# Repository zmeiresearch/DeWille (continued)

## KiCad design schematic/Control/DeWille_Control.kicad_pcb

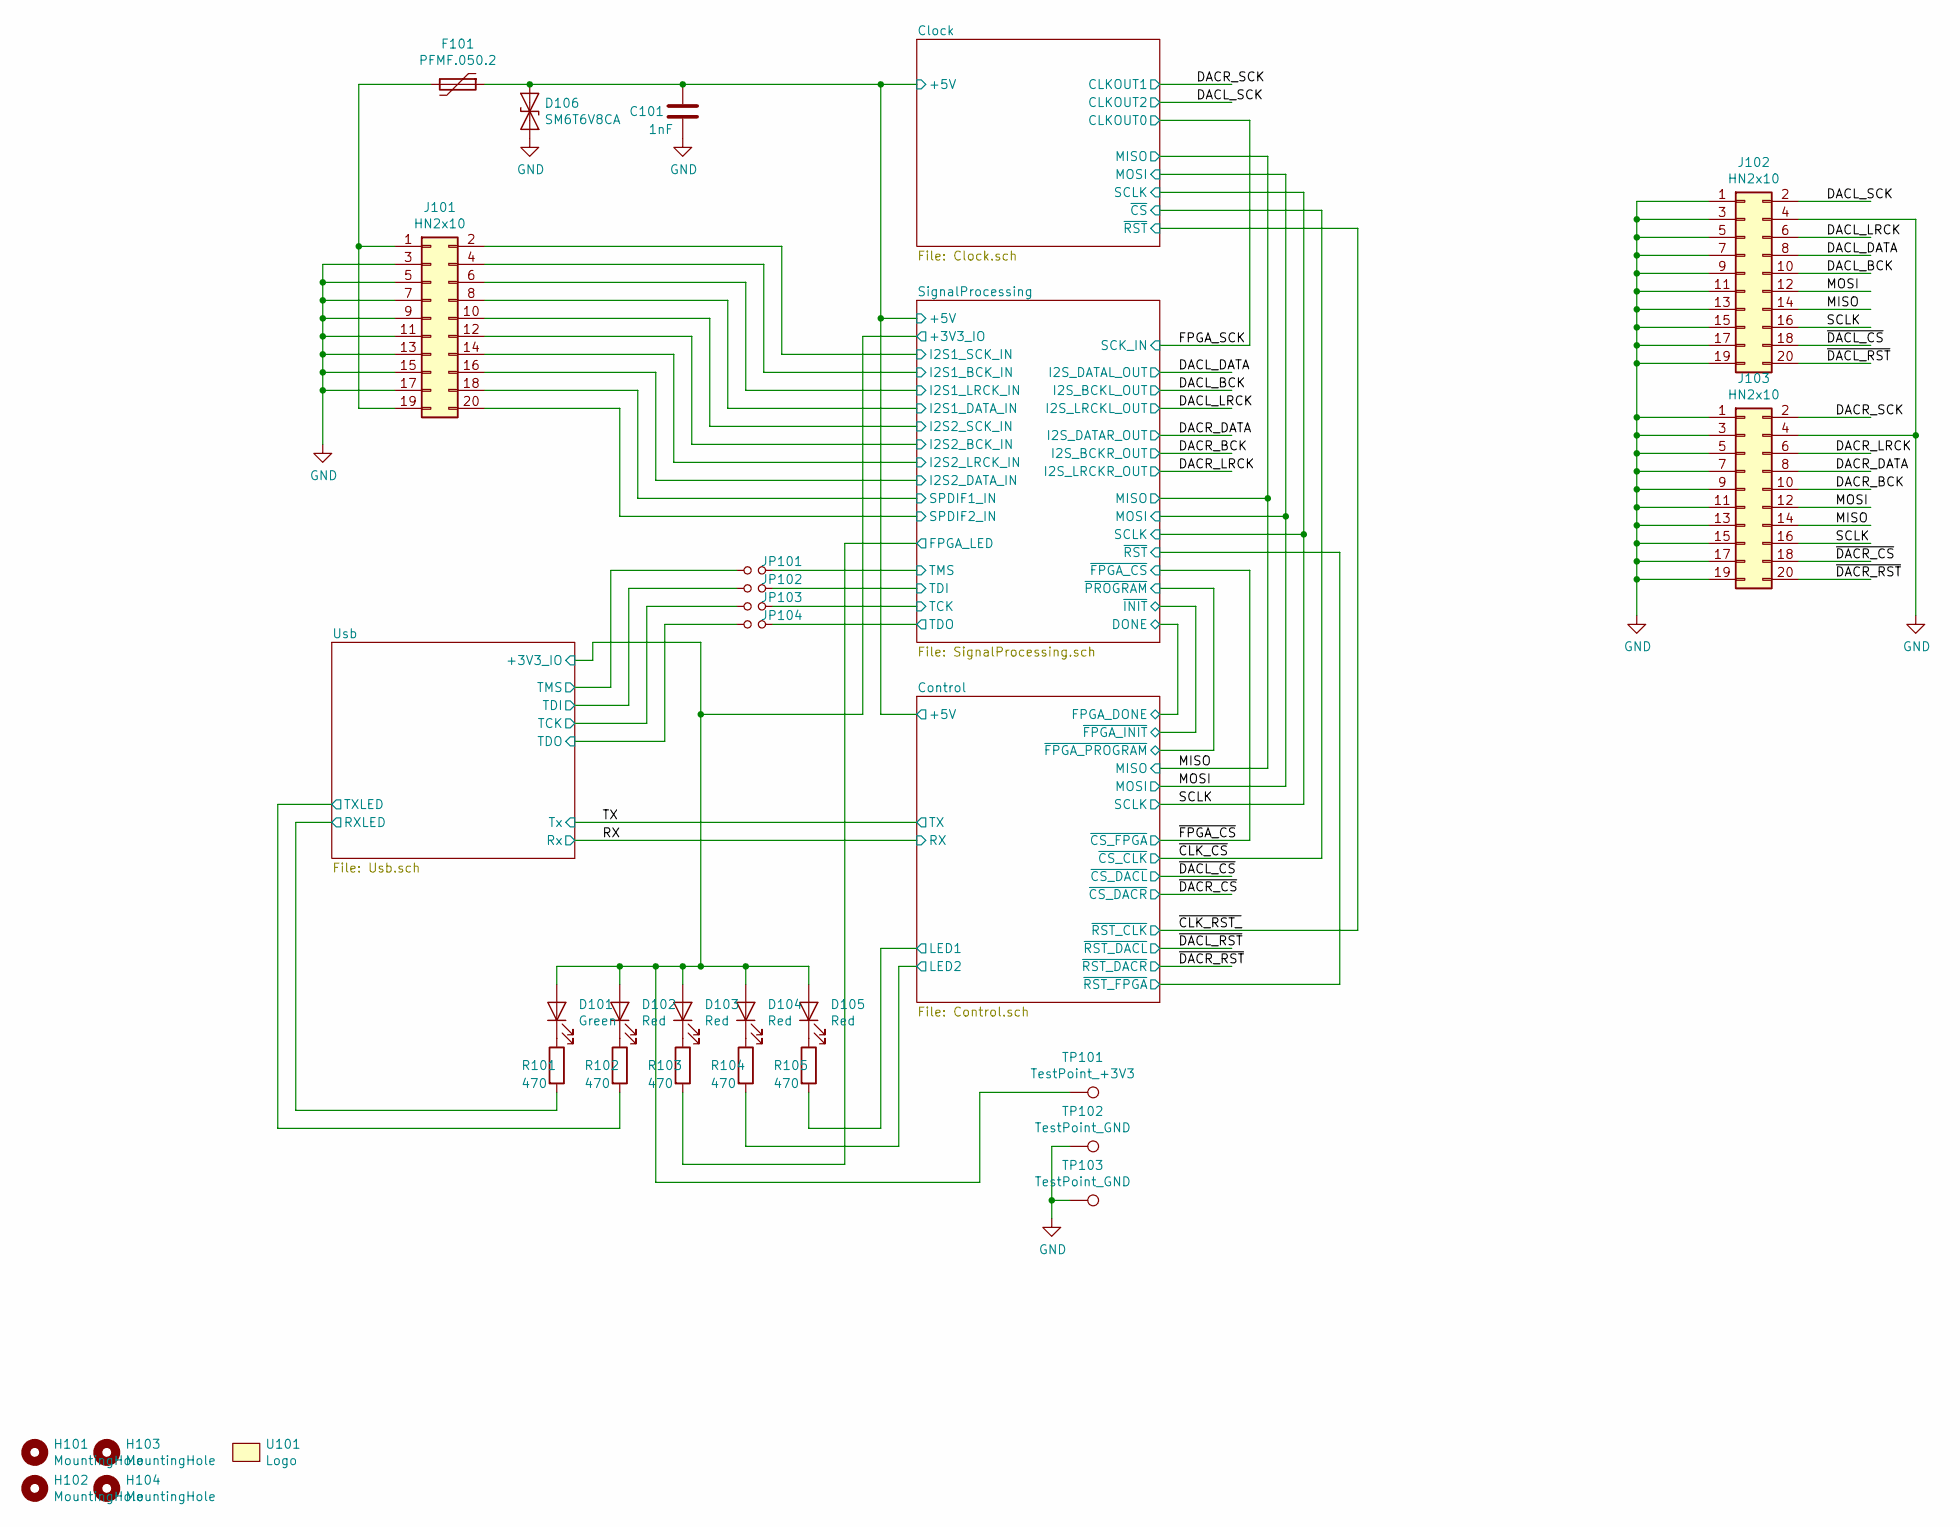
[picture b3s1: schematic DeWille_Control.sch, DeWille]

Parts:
C101: 1nF; C_0603_1608Metric
D101: Green; LED_0805_2012Metric
D102, D103, D104, D105: Red; LED_0805_2012Metric
D106: SM6T6V8CA; D_SMB
F101: PFMF.050.2; Fuse_1812_4532Metric
H101, H102, H103, H104: MountingHole; MountingHole_3.2mm_M3_Pad
J101, J102, J103: HN2x10; PinHeader_2x10_P2.54mm_Vertical
JP101, JP102, JP103, JP104: SolderJumper-2_P1.3mm_Bridged_RoundedPad1.0x1.5mm
R101, R102, R103, R104, R105: 470; R_0603_1608Metric
TP101: TestPoint_+3V3; TestPoint_THTPad_D2.0mm_Drill1.0mm
TP102, TP103: TestPoint_GND; TestPoint_THTPad_D2.0mm_Drill1.0mm
U101: Logo; Zmei-logo-small-inverted_nosilk

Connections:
/Clock/+5V: C101.2, D106.1 (A1), F101.1; also elsewhere on the board
/Control/LED1: R105.2; also elsewhere on the board
/Control/LED2: R104.2; also elsewhere on the board
/DACL_BCK: J102.10; also elsewhere on the board
/DACL_DATA: J102.8; also elsewhere on the board
/DACL_LRCK: J102.6; also elsewhere on the board
/DACL_SCK: J102.2; also elsewhere on the board
/DACR_BCK: J103.10; also elsewhere on the board
/DACR_DATA: J103.8; also elsewhere on the board
/DACR_LRCK: J103.6; also elsewhere on the board
/DACR_SCK: J103.2; also elsewhere on the board
/MISO: J102.14, J103.14; also elsewhere on the board
/MOSI: J102.12, J103.12; also elsewhere on the board
/SCLK: J102.16, J103.16; also elsewhere on the board
/SignalProcessing/+3V3_IO: D101.2 (A), D102.2 (A), D103.2 (A), D104.2 (A), D105.2 (A), TP101.1; also elsewhere on the board
/SignalProcessing/FPGA_LED: R103.2; also elsewhere on the board
/SignalProcessing/I2S1_BCK_IN: J101.4; also elsewhere on the board
/SignalProcessing/I2S1_DATA_IN: J101.8; also elsewhere on the board
/SignalProcessing/I2S1_LRCK_IN: J101.6; also elsewhere on the board
/SignalProcessing/I2S1_SCK_IN: J101.2; also elsewhere on the board
/SignalProcessing/I2S2_BCK_IN: J101.12; also elsewhere on the board
/SignalProcessing/I2S2_DATA_IN: J101.16; also elsewhere on the board
/SignalProcessing/I2S2_LRCK_IN: J101.14; also elsewhere on the board
/SignalProcessing/I2S2_SCK_IN: J101.10; also elsewhere on the board
/SignalProcessing/SPDIF1_IN: J101.18; also elsewhere on the board
/SignalProcessing/SPDIF2_IN: J101.20; also elsewhere on the board
/SignalProcessing/TCK: JP103.2; also elsewhere on the board
/SignalProcessing/TDI: JP102.2; also elsewhere on the board
/SignalProcessing/TDO: JP104.2; also elsewhere on the board
/SignalProcessing/TMS: JP101.2; also elsewhere on the board
/Usb/RXLED: R101.2; also elsewhere on the board
/Usb/TCK: JP103.1; also elsewhere on the board
/Usb/TDI: JP102.1; also elsewhere on the board
/Usb/TDO: JP104.1; also elsewhere on the board
/Usb/TMS: JP101.1; also elsewhere on the board
/Usb/TXLED: R102.2; also elsewhere on the board
/~DACL_CS~: J102.18; also elsewhere on the board
/~DACL_RST~: J102.20; also elsewhere on the board
/~DACR_CS~: J103.18; also elsewhere on the board
/~DACR_RST~: J103.20; also elsewhere on the board
GND: C101.1, D106.2 (A2), J101.3, J101.5, J101.7, J101.9, J101.11, J101.13, J101.15, J101.17, J102.1, J102.3, J102.4, J102.5, J102.7, J102.9, J102.11, J102.13, J102.15, J102.17, J102.19, J103.1, J103.3, J103.4, J103.5, J103.7, J103.9, J103.11, J103.13, J103.15, J103.17, J103.19, TP102.1, TP103.1; also elsewhere on the board
unnamed: D101.1 (K), R101.1
unnamed: D102.1 (K), R102.1
unnamed: D103.1 (K), R103.1
unnamed: D104.1 (K), R104.1
unnamed: D105.1 (K), R105.1
unnamed: F101.2, J101.1, J101.19

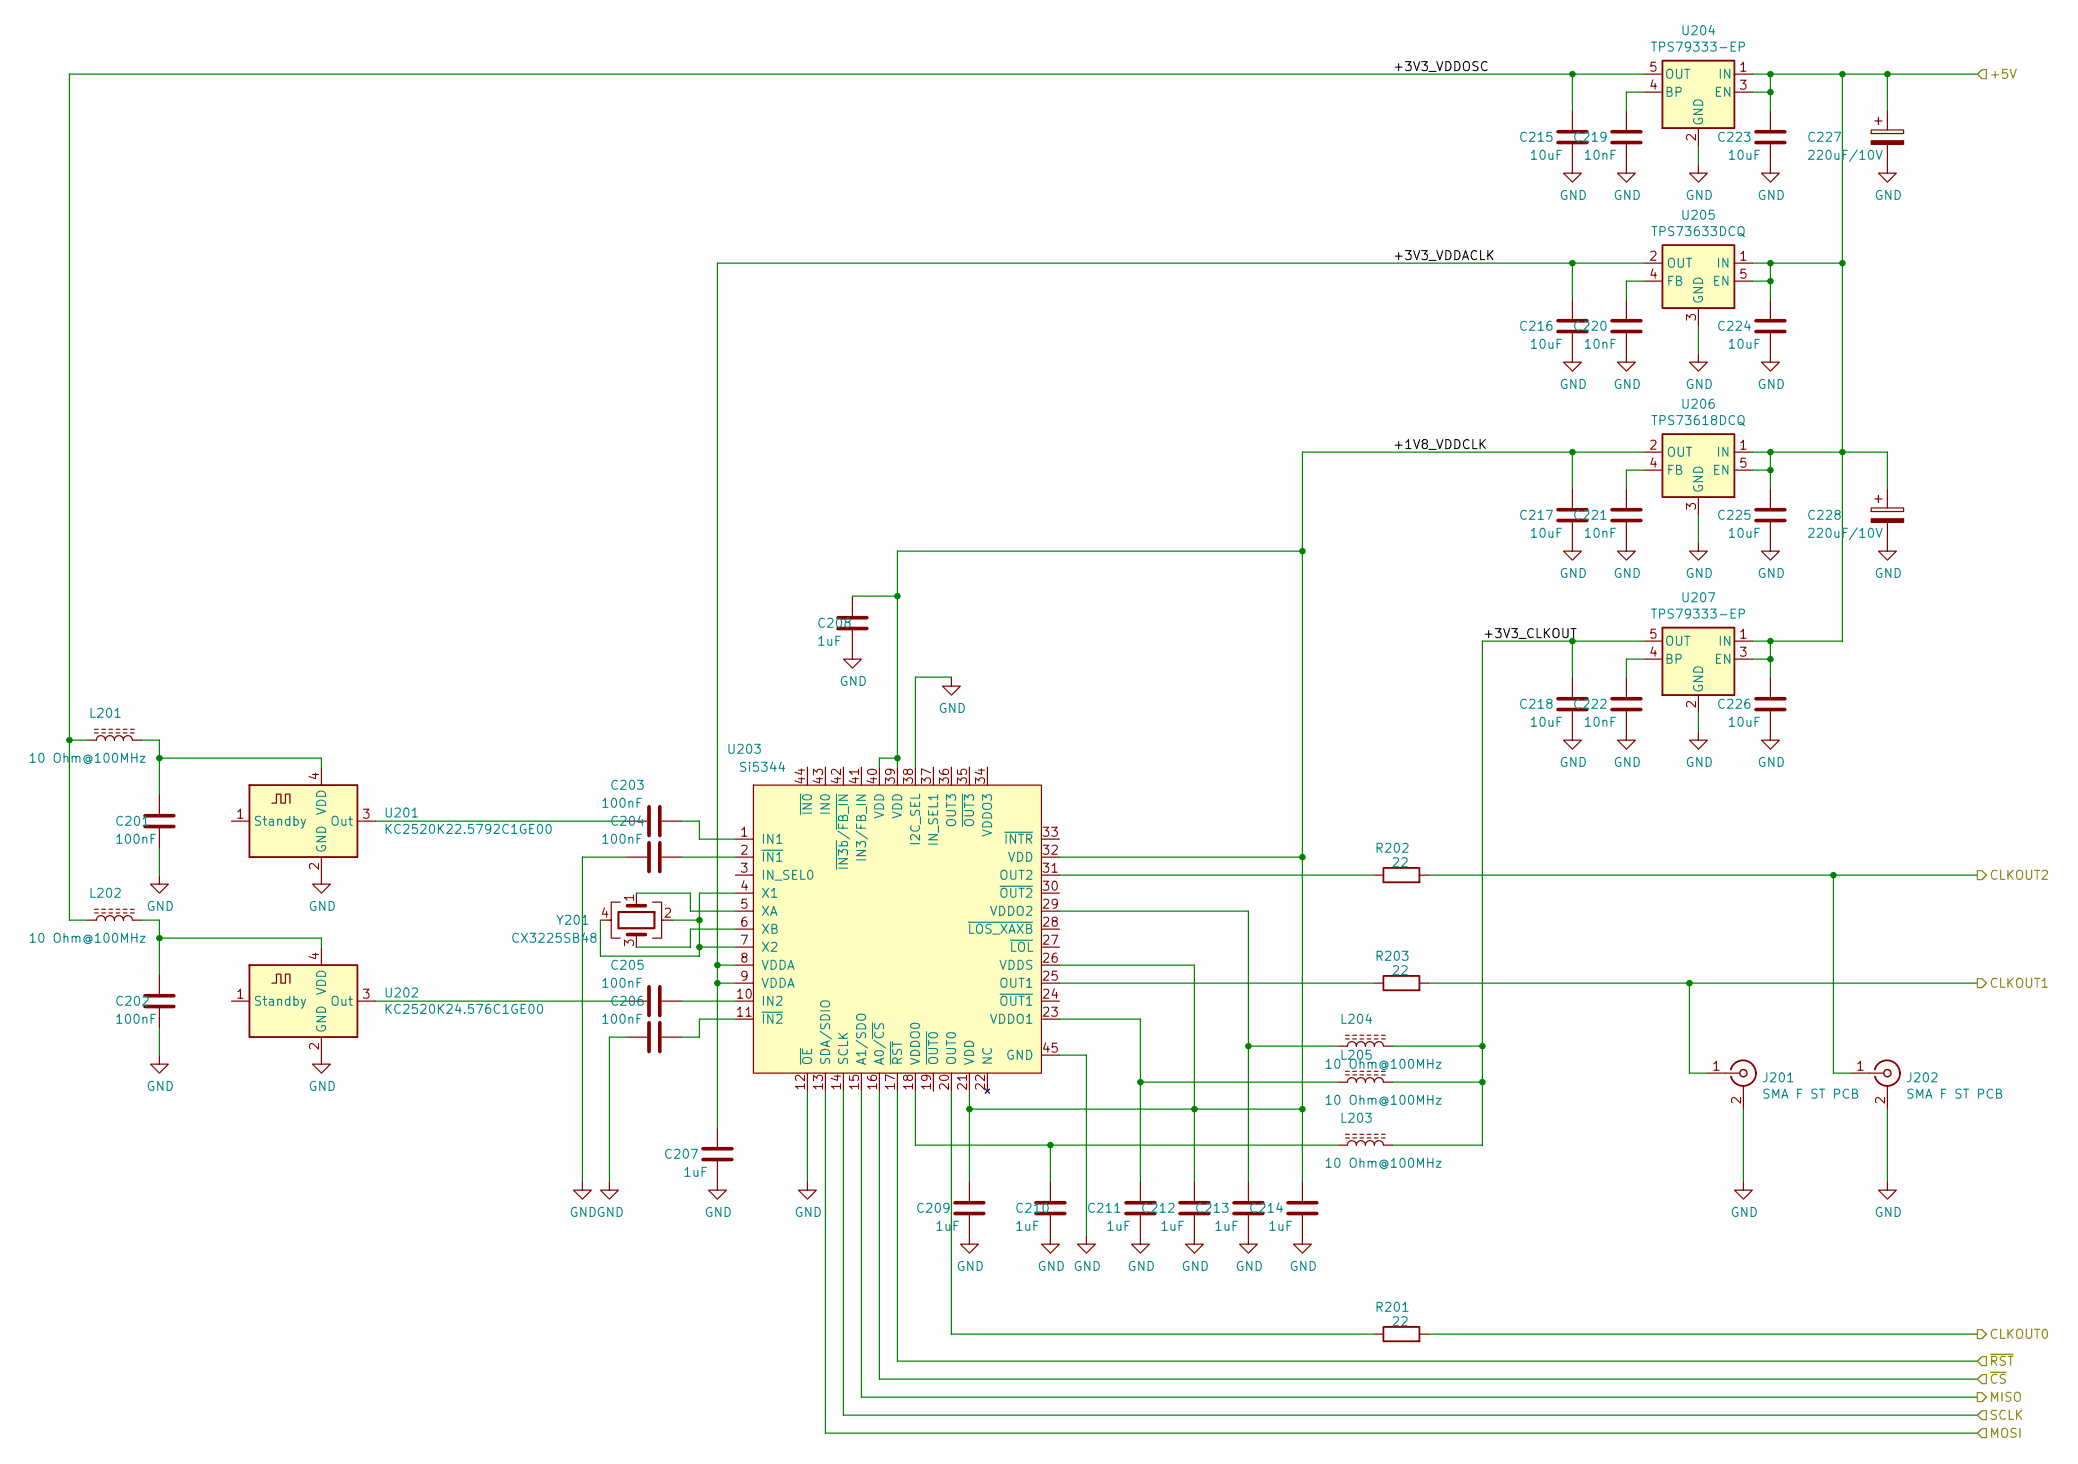
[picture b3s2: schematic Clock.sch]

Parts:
C201, C202, C203, C204, C205, C206: 100nF; C_0603_1608Metric
C207, C208, C209, C210, C211, C212, C213, C214: 1uF; C_0603_1608Metric
C215, C216, C217, C218, C223, C224, C225, C226: 10uF; C_0603_1608Metric
C219, C220, C221, C222: 10nF; C_0603_1608Metric
C227, C228: 220uF/10V; C_Elec_8x6.2
J201, J202: SMA F ST PCB; SMA_Amphenol_132134_Vertical
L201, L202, L203, L204, L205: 10 Ohm@100MHz; L_0805_2012Metric
R201, R202, R203: 22; R_0603_1608Metric
U201: KC2520K22.5792C1GE00; Oscillator_SMD_Abracon_ASDMB-4Pin_2.5x2.0mm
U202: KC2520K24.576C1GE00; Oscillator_SMD_Abracon_ASDMB-4Pin_2.5x2.0mm
U203: Si5344; QFN-44-1EP_7x7mm_P0.5mm_EP5.2x5.2mm
U204, U207: TPS79333-EP; SOT-23-5
U205: TPS73633DCQ; SOT-223-6_TabPin3
U206: TPS73618DCQ; SOT-223-6_TabPin3
Y201: CX3225SB48; Crystal_SMD_3225-4Pin_3.2x2.5mm

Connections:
/Clock/+1V8_VDDCLK: C208.1, C209.2, C212.2, C214.2, C217.2, U203.21 (VDD), U203.26 (VDDS), U203.32 (VDD), U203.39 (VDD), U203.40 (VDD), U206.2 (OUT)
/Clock/+3V3_CLKOUT: C218.2, L203.2, L204.2, L205.2, U207.5 (OUT)
/Clock/+3V3_VDDACLK: C207.2, C216.2, U203.8 (VDDA), U203.9 (VDDA), U205.2 (OUT)
/Clock/+3V3_VDDOSC: C215.2, L201.1, L202.1, U204.5 (OUT)
/Clock/+5V: C223.2, C224.2, C225.2, C226.2, C227.1, C228.1, U204.1 (IN), U204.3 (EN), U205.1 (IN), U205.5 (EN), U206.1 (IN), U206.5 (EN), U207.1 (IN), U207.3 (EN); also elsewhere on the board
/DACL_SCK: J202.1 (In), R202.2; also elsewhere on the board
/DACR_SCK: J201.1 (In), R203.2; also elsewhere on the board
/FPGA_SCK: R201.2; also elsewhere on the board
/MISO: U203.15 (A1/SDO); also elsewhere on the board
/MOSI: U203.13 (SDA/SDIO); also elsewhere on the board
/SCLK: U203.14 (SCLK); also elsewhere on the board
/~CLK_CS~: U203.16 (A0/~CS~); also elsewhere on the board
/~CLK_RST_: U203.17 (~RST~); also elsewhere on the board
GND: C201.2, C202.2, C204.2, C206.2, C207.1, C208.2, C209.1, C210.2, C211.1, C212.1, C213.1, C214.1, C215.1, C216.1, C217.1, C218.1, C219.1, C220.1, C221.1, C222.1, C223.1, C224.1, C225.1, C226.1, C227.2, C228.2, J201.2 (Ext), J202.2 (Ext), U201.2 (GND), U202.2 (GND), U203.12 (~OE~), U203.38 (I2C_SEL), U203.45 (GND), U204.2 (GND), U205.3 (GND), U206.3 (GND), U207.2 (GND); also elsewhere on the board
unnamed: C201.1, L201.2, U201.4 (VDD)
unnamed: C202.1, L202.2, U202.4 (VDD)
unnamed: C203.1, U203.1 (IN1)
unnamed: C203.2, U201.3 (Out)
unnamed: C204.1, U203.2 (~IN1~)
unnamed: C205.1, U203.10 (IN2)
unnamed: C205.2, U202.3 (Out)
unnamed: C206.1, U203.11 (~IN2~)
unnamed: C210.1, L203.1, U203.18 (VDDO0)
unnamed: C211.2, L205.1, U203.23 (VDDO1)
unnamed: C213.2, L204.1, U203.29 (VDDO2)
unnamed: C219.2, U204.4 (BP)
unnamed: C220.2, U205.4 (FB)
unnamed: C221.2, U206.4 (FB)
unnamed: C222.2, U207.4 (BP)
unnamed: R201.1, U203.20 (OUT0)
unnamed: R202.1, U203.31 (OUT2)
unnamed: R203.1, U203.25 (OUT1)
unnamed: U203.4 (X1), U203.7 (X2), Y201.2, Y201.4
unnamed: U203.5 (XA), Y201.1
unnamed: U203.6 (XB), Y201.3

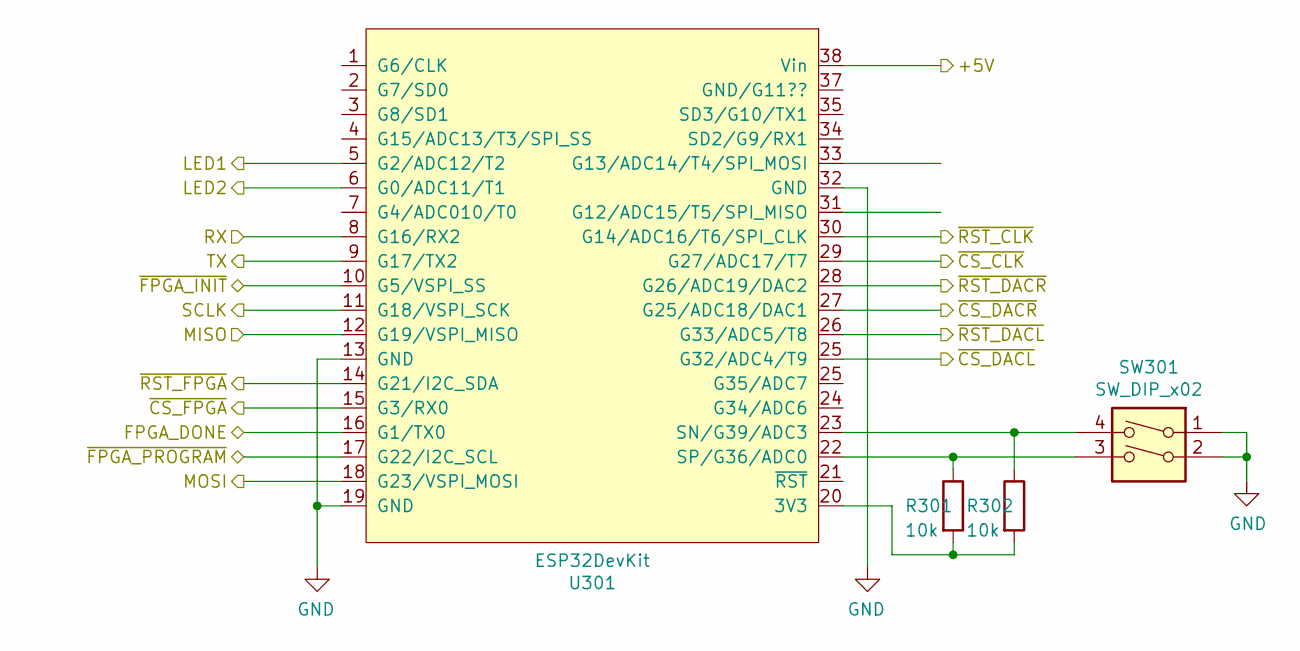
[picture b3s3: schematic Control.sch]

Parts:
R301, R302: 10k; R_0603_1608Metric
SW301: SW_DIP_x02; DIP-4_W7.62mm
U301: ESP32DevKit

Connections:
/Clock/+5V: U301.38 (Vin); also elsewhere on the board
/Control/LED1: U301.5 (G2/ADC12/T2); also elsewhere on the board
/Control/LED2: U301.6 (G0/ADC11/T1); also elsewhere on the board
/Control/~FPGA_INIT~: U301.10 (G5/VSPI_SS); also elsewhere on the board
/Control/~FPGA_PROGRAM~: U301.17 (G22/I2C_SCL); also elsewhere on the board
/Control/~RST_FPGA~: U301.14 (G21/I2C_SDA); also elsewhere on the board
/MISO: U301.12 (G19/VSPI_MISO); also elsewhere on the board
/MOSI: U301.18 (G23/VSPI_MOSI); also elsewhere on the board
/RX: U301.8 (G16/RX2); also elsewhere on the board
/SCLK: U301.11 (G18/VSPI_SCK); also elsewhere on the board
/SignalProcessing/DONE: U301.16 (G1/TX0); also elsewhere on the board
/TX: U301.9 (G17/TX2); also elsewhere on the board
/~CLK_CS~: U301.29 (G27/ADC17/T7); also elsewhere on the board
/~CLK_RST_: U301.30 (G14/ADC16/T6/SPI_CLK); also elsewhere on the board
/~DACL_CS~: U301.25 (G32/ADC4/T9); also elsewhere on the board
/~DACL_RST~: U301.26 (G33/ADC5/T8); also elsewhere on the board
/~DACR_CS~: U301.27 (G25/ADC18/DAC1); also elsewhere on the board
/~DACR_RST~: U301.28 (G26/ADC19/DAC2); also elsewhere on the board
/~FPGA_CS~: U301.15 (G3/RX0); also elsewhere on the board
GND: SW301.1, SW301.2, U301.13 (GND), U301.19 (GND), U301.32 (GND); also elsewhere on the board
unnamed: R301.1, SW301.3, U301.22 (SP/G36/ADC0)
unnamed: R301.2, R302.2, U301.20 (3V3)
unnamed: R302.1, SW301.4, U301.23 (SN/G39/ADC3)

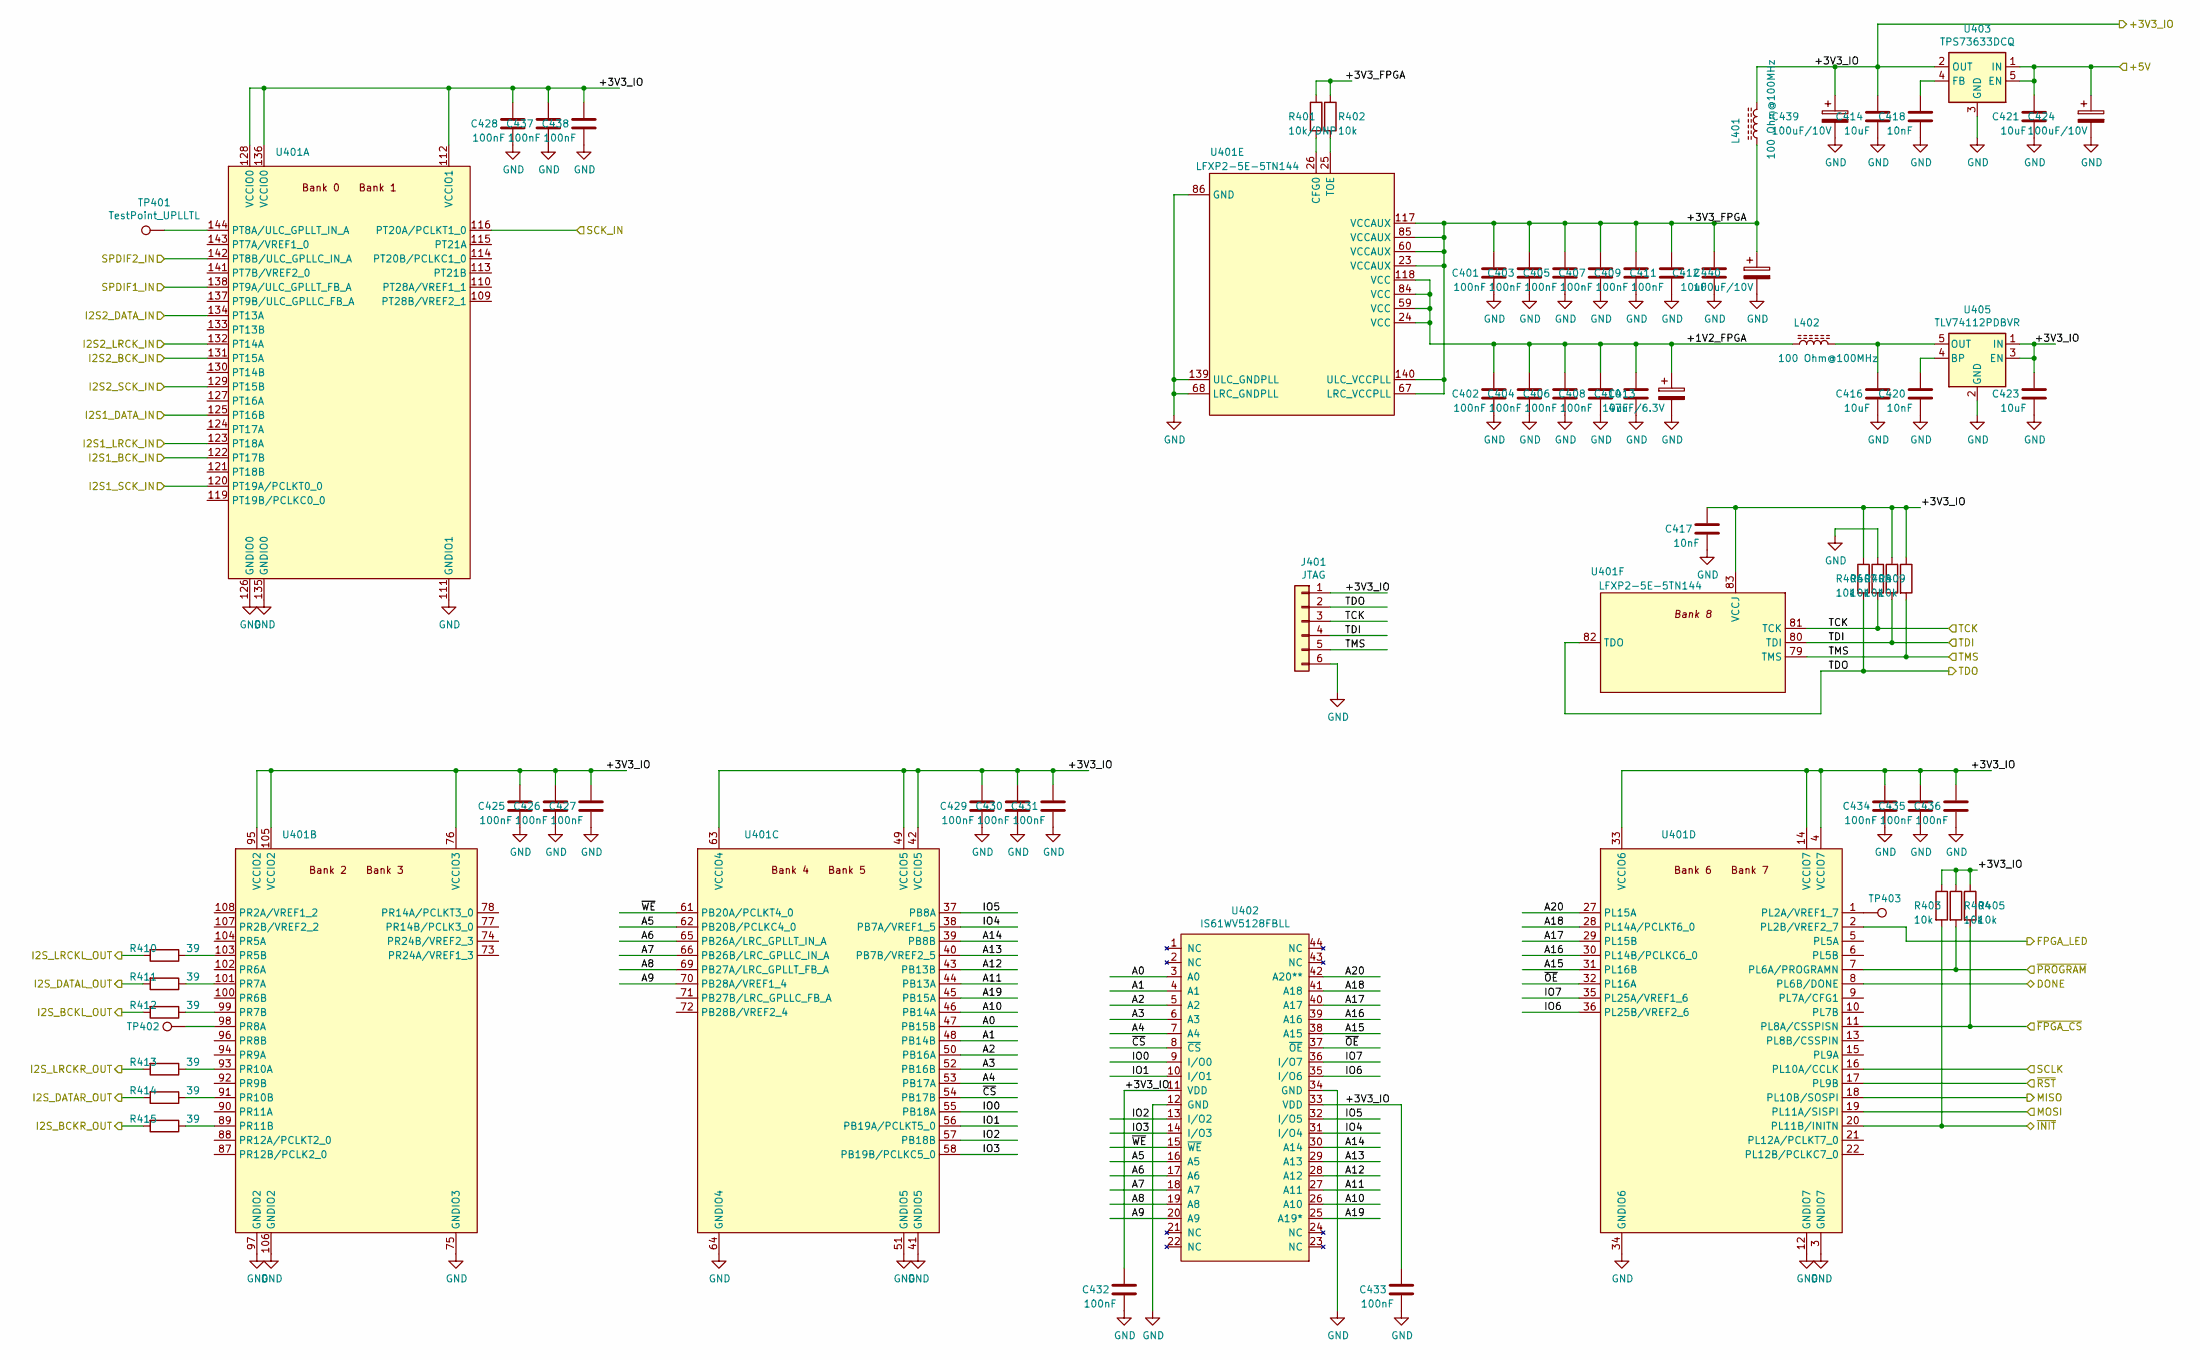
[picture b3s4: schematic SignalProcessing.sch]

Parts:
C401, C402, C403, C404, C405, C406, C407, C408, C409, C411, C425, C426, C427, C428, C429, C430, C431, C432, C433, C434, C435, C436, C437, C438: 100nF; C_0603_1608Metric
C410, C412, C414, C416, C421, C423: 10uF; C_0603_1608Metric
C413: 47uF/6.3V; CP_EIA-3528-12_Kemet-T
C417, C418, C420: 10nF; C_0603_1608Metric
C424, C439, C440: 100uF/10V; C_Elec_6.3x5.4
J401: JTAG; PinHeader_1x06_P2.54mm_Vertical
L401, L402: 100 Ohm@100MHz; L_0805_2012Metric
R401: 10k/DNP; R_0603_1608Metric
R402, R403, R404, R405, R406, R407, R408, R409: 10k; R_0603_1608Metric
R410, R411, R412, R413, R414, R415: 39; R_0603_1608Metric
TP401: TestPoint_UPLLTL; TestPoint_Pad_D1.0mm
TP402: TestPoint_free2; TestPoint_Pad_D1.0mm
TP403: TP_free1; TestPoint_Pad_D1.0mm
U401: LFXP2-5E-5TN144; TQFP-144_20x20mm_P0.5mm
U402: IS61WV5128FBLL; TSOP-II-44_10.16x18.41mm_P0.8mm
U403: TPS73633DCQ; SOT-223-6_TabPin3
U405: TLV74112PDBVR; SOT-23-5

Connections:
/Clock/+5V: C421.2, C424.1, U403.1 (IN), U403.5 (EN); also elsewhere on the board
/Control/~FPGA_INIT~: R403.2, U401.20 (PL11B/INITN); also elsewhere on the board
/Control/~FPGA_PROGRAM~: R404.2, U401.7 (PL6A/PROGRAMN); also elsewhere on the board
/Control/~RST_FPGA~: U401.17 (PL9B); also elsewhere on the board
/DACL_BCK: R412.2; also elsewhere on the board
/DACL_DATA: R411.2; also elsewhere on the board
/DACL_LRCK: R410.2; also elsewhere on the board
/DACR_BCK: R415.2; also elsewhere on the board
/DACR_DATA: R414.2; also elsewhere on the board
/DACR_LRCK: R413.2; also elsewhere on the board
/FPGA_SCK: U401.116 (PT20A/PCLKT1_0); also elsewhere on the board
/MISO: U401.18 (PL10B/SOSPI); also elsewhere on the board
/MOSI: U401.19 (PL11A/SISPI); also elsewhere on the board
/SCLK: U401.16 (PL10A/CCLK); also elsewhere on the board
/SignalProcessing/+1V2_FPGA: C402.2, C404.2, C406.2, C408.2, C410.2, C413.1, L402.1, U401.24 (VCC), U401.59 (VCC), U401.84 (VCC), U401.118 (VCC)
/SignalProcessing/+3V3_FPGA: C401.2, C403.2, C405.2, C407.2, C409.2, C411.2, C412.2, C440.1, L401.1, R401.1, R402.1, U401.23 (VCCAUX), U401.60 (VCCAUX), U401.67 (LRC_VCCPLL), U401.85 (VCCAUX), U401.117 (VCCAUX), U401.140 (ULC_VCCPLL)
/SignalProcessing/+3V3_IO: C414.2, C417.2, C423.2, C425.2, C426.2, C427.2, C428.2, C429.2, C430.2, C431.2, C432.2, C433.2, C434.2, C435.2, C436.2, C437.2, C438.2, C439.1, J401.1, L401.2, R403.1, R404.1, R405.1, R406.1, R408.1, R409.1, U401.4 (VCCIO7), U401.14 (VCCIO7), U401.33 (VCCIO6), U401.42 (VCCIO5), U401.49 (VCCIO5), U401.63 (VCCIO4), U401.76 (VCCIO3), U401.83 (VCCJ), U401.95 (VCCIO2), U401.105 (VCCIO2), U401.112 (VCCIO1), U401.128 (VCCIO0), U401.136 (VCCIO0), U402.11 (VDD), U402.33 (VDD), U403.2 (OUT), U405.1 (IN), U405.3 (EN); also elsewhere on the board
/SignalProcessing/A0: U401.47 (PB15B), U402.3 (A0)
/SignalProcessing/A1: U401.48 (PB14B), U402.4 (A1)
/SignalProcessing/A2: U401.50 (PB16A), U402.5 (A2)
/SignalProcessing/A3: U401.52 (PB16B), U402.6 (A3)
/SignalProcessing/A4: U401.53 (PB17A), U402.7 (A4)
/SignalProcessing/A5: U401.62 (PB20B/PCLKC4_0), U402.16 (A5)
/SignalProcessing/A6: U401.65 (PB26A/LRC_GPLLT_IN_A), U402.17 (A6)
/SignalProcessing/A7: U401.66 (PB26B/LRC_GPLLC_IN_A), U402.18 (A7)
/SignalProcessing/A8: U401.69 (PB27A/LRC_GPLLT_FB_A), U402.19 (A8)
/SignalProcessing/A9: U401.70 (PB28A/VREF1_4), U402.20 (A9)
/SignalProcessing/A10: U401.46 (PB14A), U402.26 (A10)
/SignalProcessing/A11: U401.44 (PB13A), U402.27 (A11)
/SignalProcessing/A12: U401.43 (PB13B), U402.28 (A12)
/SignalProcessing/A13: U401.40 (PB7B/VREF2_5), U402.29 (A13)
/SignalProcessing/A14: U401.39 (PB8B), U402.30 (A14)
/SignalProcessing/A15: U401.31 (PL16B), U402.38 (A15)
/SignalProcessing/A16: U401.30 (PL14B/PCLKC6_0), U402.39 (A16)
/SignalProcessing/A17: U401.29 (PL15B), U402.40 (A17)
/SignalProcessing/A18: U401.28 (PL14A/PCLKT6_0), U402.41 (A18)
/SignalProcessing/A19: U401.45 (PB15A), U402.25 (A19*)
/SignalProcessing/A20: U401.27 (PL15A), U402.42 (A20**)
/SignalProcessing/DONE: U401.8 (PL6B/DONE); also elsewhere on the board
/SignalProcessing/FPGA_LED: U401.2 (PL2B/VREF2_7); also elsewhere on the board
/SignalProcessing/I2S1_BCK_IN: U401.122 (PT17B); also elsewhere on the board
/SignalProcessing/I2S1_DATA_IN: U401.125 (PT16B); also elsewhere on the board
/SignalProcessing/I2S1_LRCK_IN: U401.123 (PT18A); also elsewhere on the board
/SignalProcessing/I2S1_SCK_IN: U401.120 (PT19A/PCLKT0_0); also elsewhere on the board
/SignalProcessing/I2S2_BCK_IN: U401.131 (PT15A); also elsewhere on the board
/SignalProcessing/I2S2_DATA_IN: U401.134 (PT13A); also elsewhere on the board
/SignalProcessing/I2S2_LRCK_IN: U401.132 (PT14A); also elsewhere on the board
/SignalProcessing/I2S2_SCK_IN: U401.129 (PT15B); also elsewhere on the board
/SignalProcessing/IO0: U401.55 (PB18A), U402.9 (I/O0)
/SignalProcessing/IO1: U401.56 (PB19A/PCLKT5_0), U402.10 (I/O1)
/SignalProcessing/IO2: U401.57 (PB18B), U402.13 (I/O2)
/SignalProcessing/IO3: U401.58 (PB19B/PCLKC5_0), U402.14 (I/O3)
/SignalProcessing/IO4: U401.38 (PB7A/VREF1_5), U402.31 (I/O4)
/SignalProcessing/IO5: U401.37 (PB8A), U402.32 (I/O5)
/SignalProcessing/IO6: U401.36 (PL25B/VREF2_6), U402.35 (I/O6)
/SignalProcessing/IO7: U401.35 (PL25A/VREF1_6), U402.36 (I/O7)
/SignalProcessing/SPDIF1_IN: U401.138 (PT9A/ULC_GPLLT_FB_A); also elsewhere on the board
/SignalProcessing/SPDIF2_IN: U401.142 (PT8B/ULC_GPLLC_IN_A); also elsewhere on the board
/SignalProcessing/TCK: J401.3, R407.2, U401.81 (TCK); also elsewhere on the board
/SignalProcessing/TDI: J401.4, R408.2, U401.80 (TDI); also elsewhere on the board
/SignalProcessing/TDO: J401.2, R406.2, U401.82 (TDO); also elsewhere on the board
/SignalProcessing/TMS: J401.5, R409.2, U401.79 (TMS); also elsewhere on the board
/SignalProcessing/~CS~: U401.54 (PB17B), U402.8 (~CS~)
/SignalProcessing/~OE~: U401.32 (PL16A), U402.37 (~OE~)
/SignalProcessing/~WE~: U401.61 (PB20A/PCLKT4_0), U402.15 (~WE~)
/~FPGA_CS~: R405.2, U401.11 (PL8A/CSSPISN); also elsewhere on the board
GND: C401.1, C402.1, C403.1, C404.1, C405.1, C406.1, C407.1, C408.1, C409.1, C410.1, C411.1, C412.1, C413.2, C414.1, C416.1, C417.1, C418.1, C420.1, C421.1, C423.1, C424.2, C425.1, C426.1, C427.1, C428.1, C429.1, C430.1, C431.1, C432.1, C433.1, C434.1, C435.1, C436.1, C437.1, C438.1, C439.2, C440.2, J401.6, R407.1, U401.3 (GNDIO7), U401.12 (GNDIO7), U401.34 (GNDIO6), U401.41 (GNDIO5), U401.51 (GNDIO5), U401.64 (GNDIO4), U401.68 (LRC_GNDPLL), U401.75 (GNDIO3), U401.86 (GND), U401.97 (GNDIO2), U401.106 (GNDIO2), U401.111 (GNDIO1), U401.126 (GNDIO0), U401.135 (GNDIO0), U401.139 (ULC_GNDPLL), U402.12 (GND), U402.34 (GND), U403.3 (GND), U405.2 (GND); also elsewhere on the board
unnamed: C416.2, L402.2, U405.5 (OUT)
unnamed: C418.2, U403.4 (FB)
unnamed: C420.2, U405.4 (BP)
unnamed: R401.2, U401.26 (CFG0)
unnamed: R402.2, U401.25 (TOE)
unnamed: R410.1, U401.103 (PR5B)
unnamed: R411.1, U401.101 (PR7A)
unnamed: R412.1, U401.99 (PR7B)
unnamed: R413.1, U401.93 (PR10A)
unnamed: R414.1, U401.91 (PR10B)
unnamed: R415.1, U401.89 (PR11B)
unnamed: TP401.1, U401.144 (PT8A/ULC_GPLLT_IN_A)
unnamed: TP402.1, U401.98 (PR8A)
unnamed: TP403.1, U401.1 (PL2A/VREF1_7)

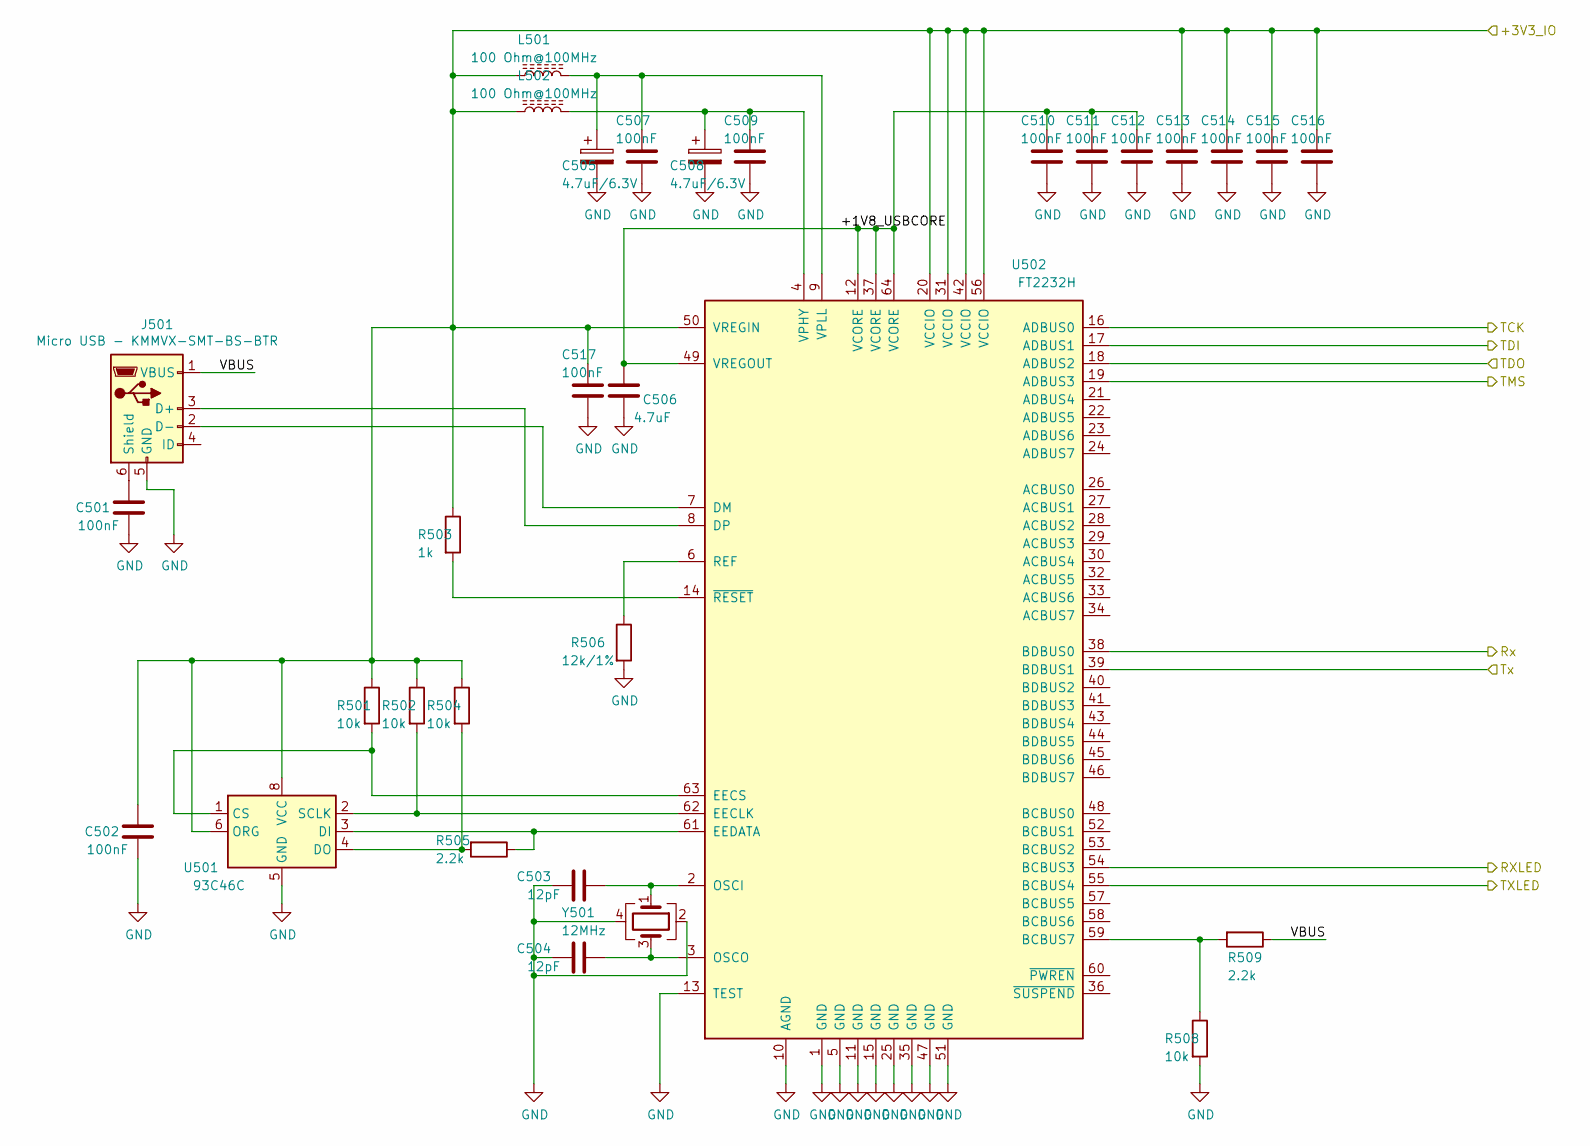
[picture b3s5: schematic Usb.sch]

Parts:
C501, C502, C507, C509, C510, C511, C512, C513, C514, C515, C516, C517: 100nF; C_0603_1608Metric
C503, C504: 12pF; C_0603_1608Metric
C505, C508: 4.7uF/6.3V; CP_EIA-3216-18_Kemet-A
C506: 4.7uF; C_0603_1608Metric
J501: Micro USB - KMMVX-SMT-BS-BTR; USB_MICRO_207A-BBA0-R
L501, L502: 100 Ohm@100MHz; L_0805_2012Metric
R501, R502, R504, R508: 10k; R_0603_1608Metric
R503: 1k; R_0603_1608Metric
R505, R509: 2.2k; R_0603_1608Metric
R506: 12k/1%; R_0603_1608Metric
U501: 93C46C; SOIC-8_3.9x4.9mm_P1.27mm
U502: FT2232H; LQFP-64_10x10mm_P0.5mm
Y501: 12MHz; Crystal_SMD_3225-4Pin_3.2x2.5mm

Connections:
/RX: U502.38 (BDBUS0); also elsewhere on the board
/SignalProcessing/+3V3_IO: C502.2, C513.1, C514.1, C515.1, C516.1, C517.1, L501.1, L502.1, R501.1, R502.1, R503.1, R504.1, U501.6 (ORG), U501.8 (VCC), U502.20 (VCCIO), U502.31 (VCCIO), U502.42 (VCCIO), U502.50 (VREGIN), U502.56 (VCCIO); also elsewhere on the board
/TX: U502.39 (BDBUS1); also elsewhere on the board
/Usb/+1V8_USBCORE: C506.1, C510.1, C511.1, C512.1, U502.12 (VCORE), U502.37 (VCORE), U502.49 (VREGOUT), U502.64 (VCORE)
/Usb/RXLED: U502.54 (BCBUS3); also elsewhere on the board
/Usb/TCK: U502.16 (ADBUS0); also elsewhere on the board
/Usb/TDI: U502.17 (ADBUS1); also elsewhere on the board
/Usb/TDO: U502.18 (ADBUS2); also elsewhere on the board
/Usb/TMS: U502.19 (ADBUS3); also elsewhere on the board
/Usb/TXLED: U502.55 (BCBUS4); also elsewhere on the board
/Usb/VBUS: J501.1 (VBUS), R509.1
GND: C501.1, C502.1, C503.1, C504.1, C505.2, C506.2, C507.2, C508.2, C509.2, C510.2, C511.2, C512.2, C513.2, C514.2, C515.2, C516.2, C517.2, J501.5 (GND), R506.2, R508.2, U501.5 (GND), U502.1 (GND), U502.5 (GND), U502.10 (AGND), U502.11 (GND), U502.13 (TEST), U502.15 (GND), U502.25 (GND), U502.35 (GND), U502.47 (GND), U502.51 (GND), Y501.2, Y501.4; also elsewhere on the board
unnamed: C501.2, J501.6 (Shield)
unnamed: C503.2, U502.2 (OSCI), Y501.1
unnamed: C504.2, U502.3 (OSCO), Y501.3
unnamed: C505.1, C507.1, L501.2, U502.9 (VPLL)
unnamed: C508.1, C509.1, L502.2, U502.4 (VPHY)
unnamed: J501.2 (D-), U502.7 (DM)
unnamed: J501.3 (D+), U502.8 (DP)
unnamed: R501.2, U501.1 (CS), U502.63 (EECS)
unnamed: R502.2, U501.2 (SCLK), U502.62 (EECLK)
unnamed: R503.2, U502.14 (~RESET)
unnamed: R504.2, R505.2, U501.4 (DO)
unnamed: R505.1, U501.3 (DI), U502.61 (EEDATA)
unnamed: R506.1, U502.6 (REF)
unnamed: R508.1, R509.2, U502.59 (BCBUS7)
